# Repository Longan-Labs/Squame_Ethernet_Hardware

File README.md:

Resources of [Squame Ethernet](https://www.longan-labs.cc/catalogsearch/result/?q=squama)

Include:

1. Eagle File
1. Datasheet for W5500

Click on [Longan-Labs.cc](https://www.longan-labs.cc/) to get the product you need.

Contact [support@longan-labs.cc](support@longan-labs.cc) if you need help.

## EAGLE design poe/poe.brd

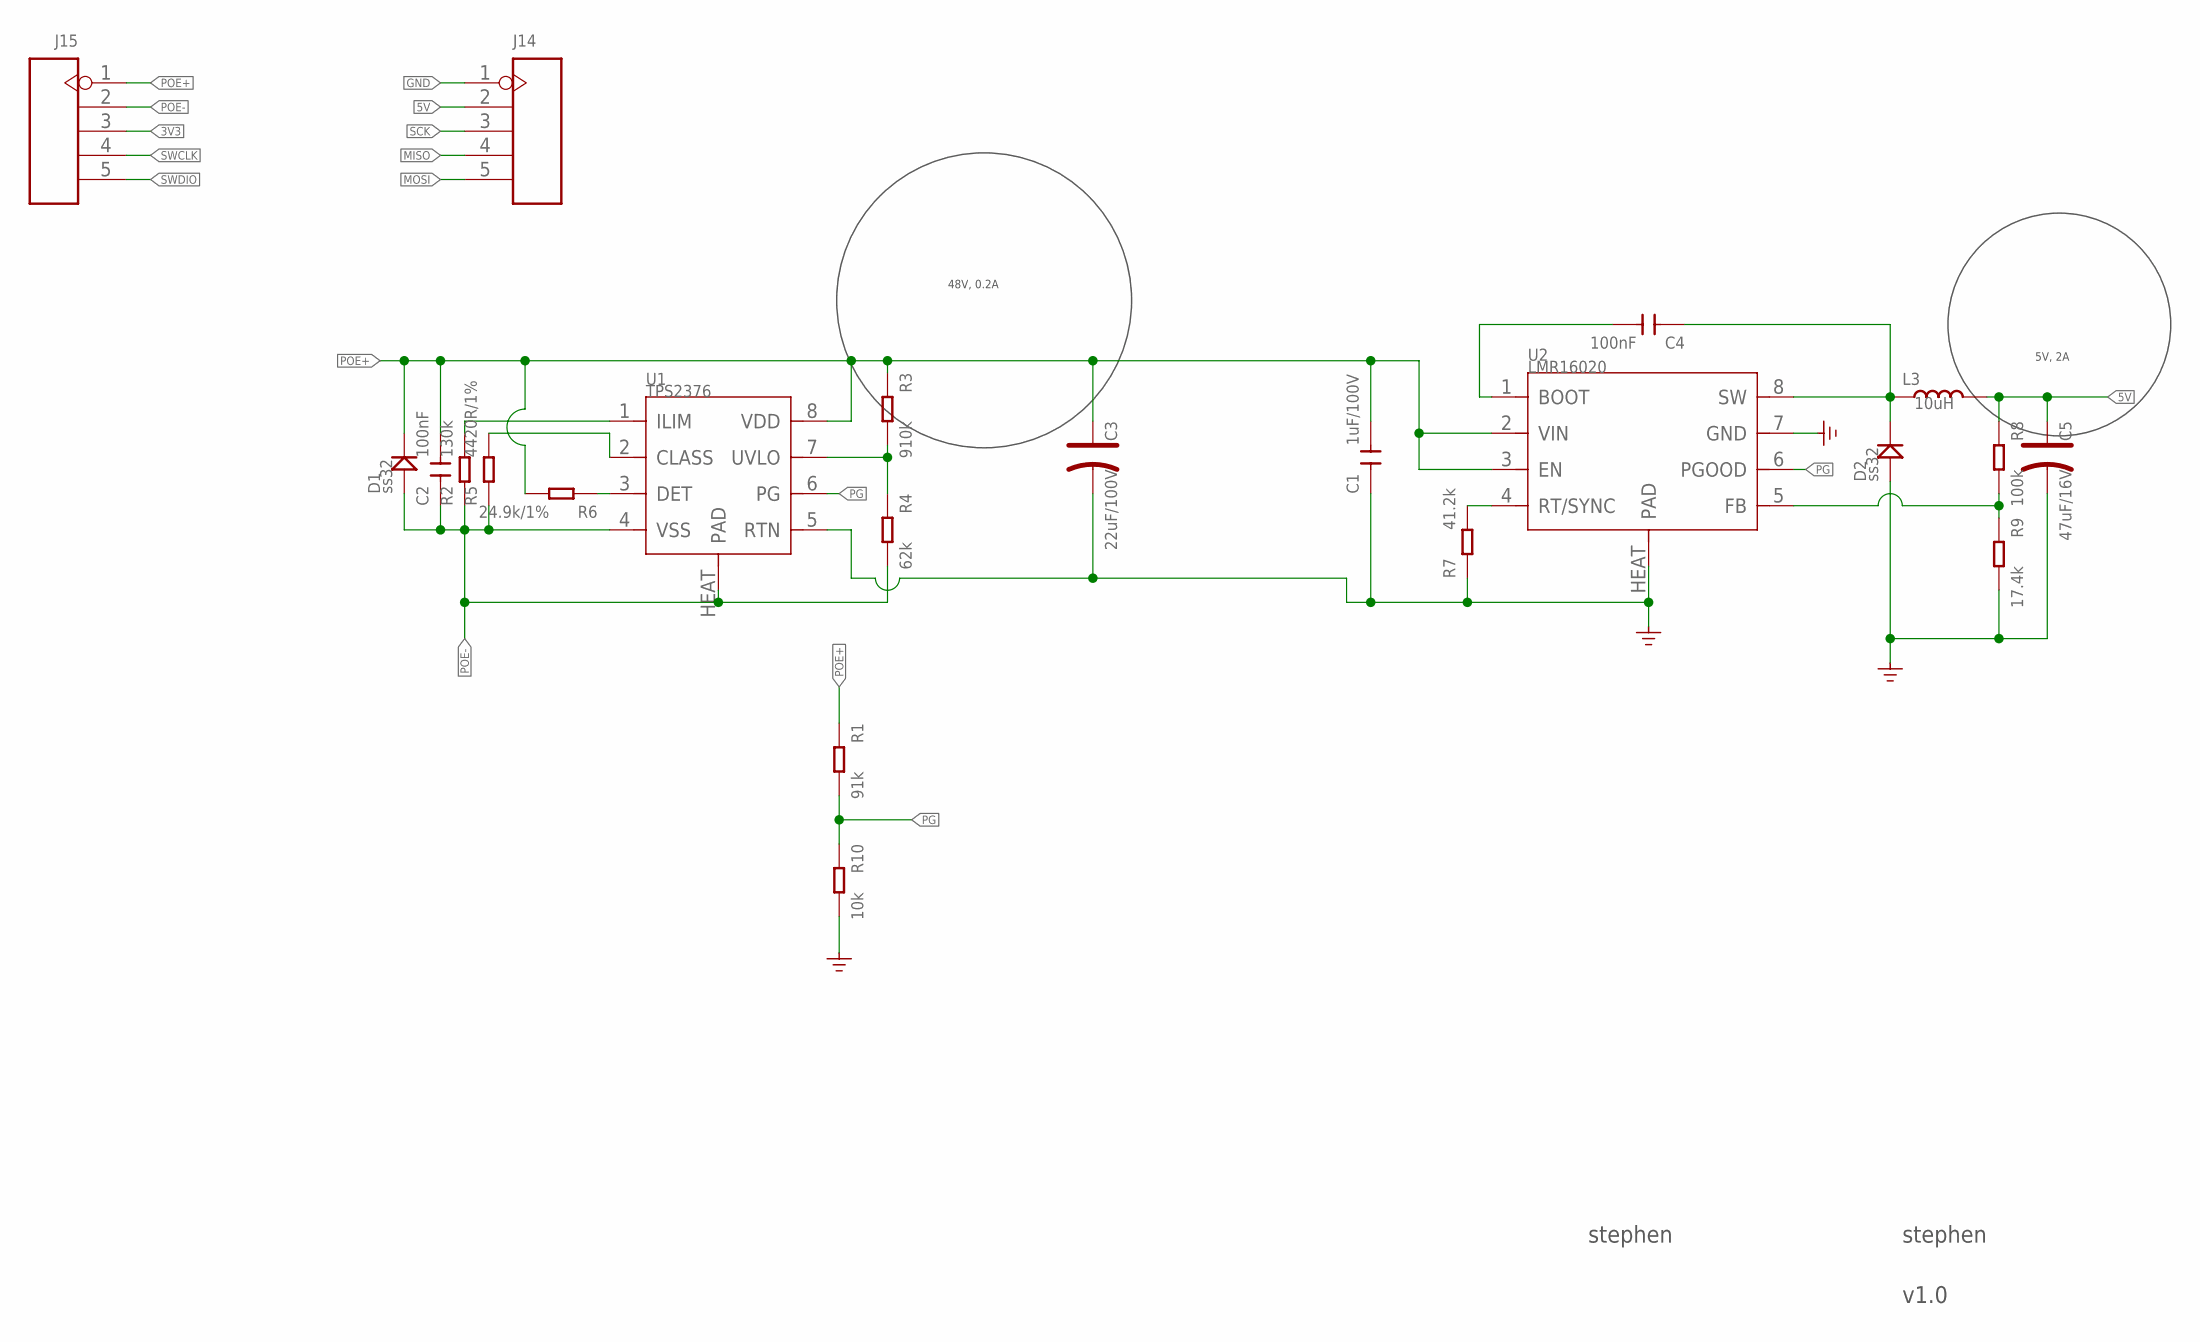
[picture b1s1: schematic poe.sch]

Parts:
C1: 1uF/100V; C0805
C2: 100nF; C0805
C3: 22uF/100V; ELECTRO-SMD-E-7.8MM
C4: 100nF; C0603
C5: 47uF/16V; AVX-B
D1, D2: ss32; DO-214AC
J14, J15: HEADER-5P-2.0; H5-2.0
L3: 10uH; INT2-SMD-6.6X7.1X3MM
R1: 91k; R0603
R2: 130k; R0603
R3: 910k; R0603
R4: 62k; R0603
R5: 4420R/1%; R0603
R6: 24.9k/1%; R0603
R7: 41.2k; R0603
R8: 100k; R0603
R9: 17.4k; R0603
R10: 10k; R0603
U1: TPS2376; SOP8G-1.27-5X3.9MM
U2: LMR16020; SOP8G-1.27-5X3.9MM

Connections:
3V3: J15.3
5V: C5.+, J14.2, L3.2, R8.1
GND: C1.1, C3.-, C5.-, D2.1 (+), J14.1, R7.1, R9.2, R10.2, U1.5 (RTN), U2.7 (GND), U2.HEAT (PAD)
MISO: J14.4
MOSI: J14.5
unnamed: R2.2, U1.1 (ILIM)
unnamed: R5.2, U1.2 (CLASS)
unnamed: R6.1, U1.3 (DET)
unnamed: C4.2, U2.1 (BOOT)
unnamed: R3.2, R4.1, U1.7 (UVLO)
unnamed: R7.2, U2.4 (RT/SYNC)
unnamed: R8.2, R9.1, U2.5 (FB)
unnamed: C4.1, D2.2 (-), L3.1, U2.8 (SW)
PG: R1.2, R10.1, U1.6 (PG), U2.6 (PGOOD)
POE+: C1.2, C2.2, C3.+, D1.2 (-), J15.1, R1.1, R3.1, R6.2, U1.8 (VDD), U2.2 (VIN), U2.3 (EN)
POE-: C2.1, D1.1 (+), J15.2, R2.1, R4.2, R5.1, U1.4 (VSS), U1.HEAT (PAD)
SCK: J14.3
SWCLK: J15.4
SWDIO: J15.5

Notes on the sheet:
stephen
v1.0
48V, 0.2A
5V, 2A

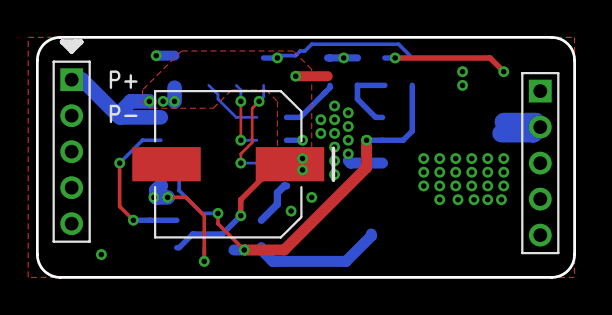
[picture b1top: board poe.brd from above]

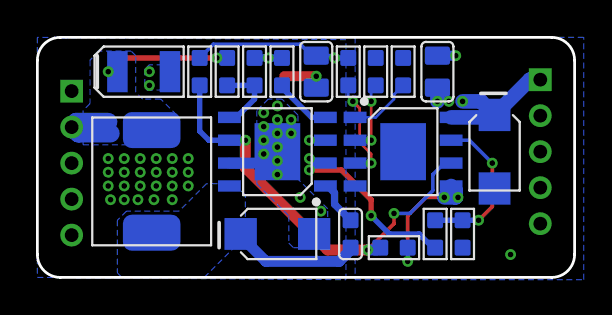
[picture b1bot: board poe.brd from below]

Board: 2 copper layers, 29.8 x 13.3 mm, 22 parts (19 on the bottom side), 13 nets.

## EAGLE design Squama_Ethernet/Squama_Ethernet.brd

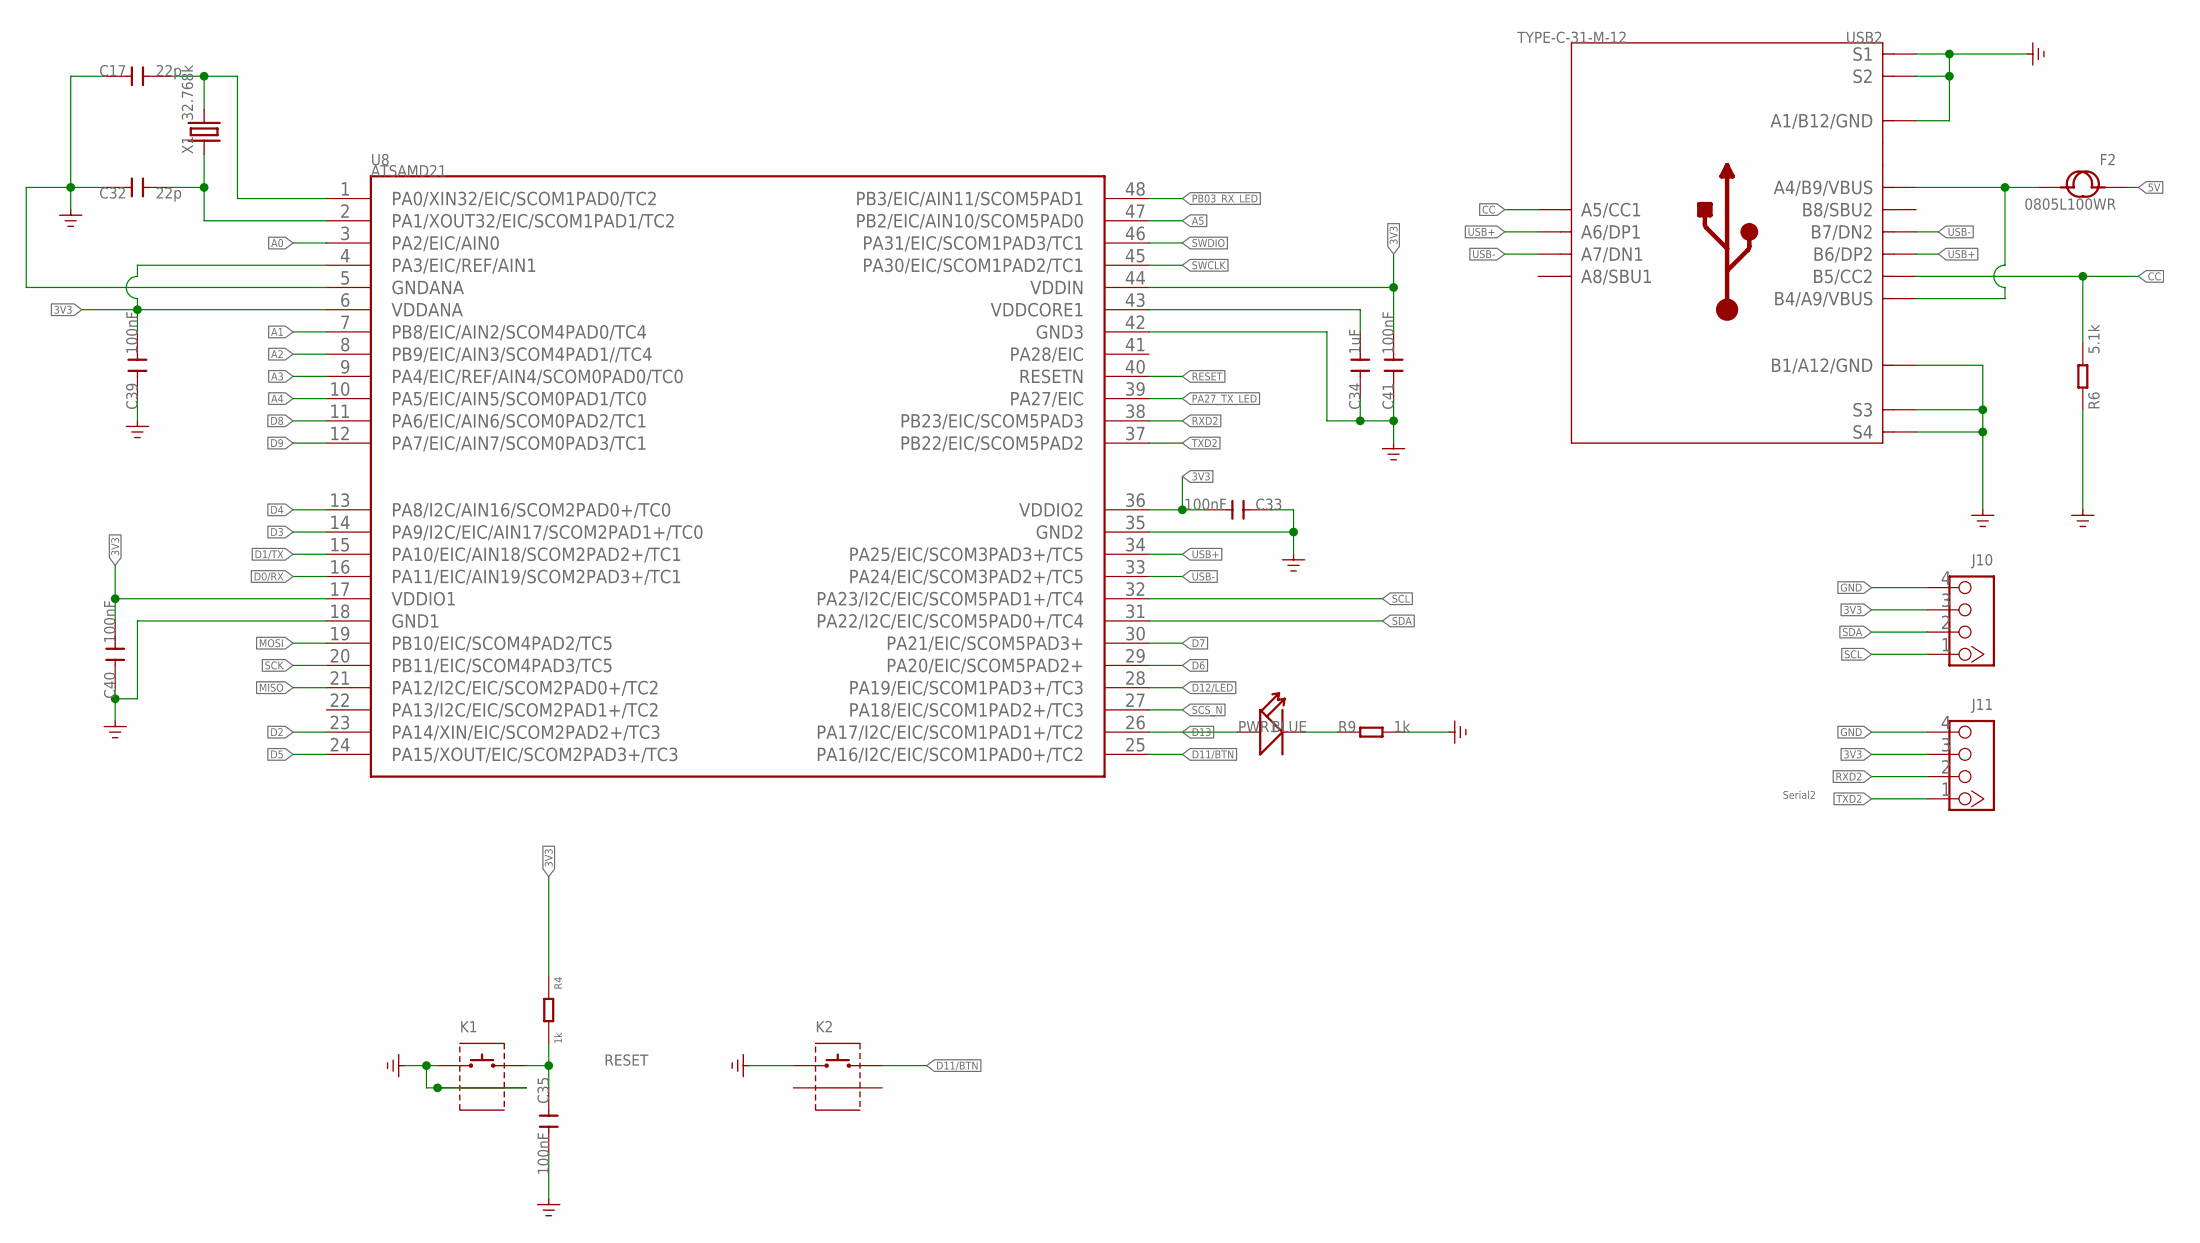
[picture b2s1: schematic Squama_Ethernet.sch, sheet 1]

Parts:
C17, C32: 22p; C0603
C33, C35, C39, C40, C41: 100nF; C0603
C34: 1uF; C0603
F2: 0805L100WR; F0805
J10, J11: 320110033; HW4-2.0
K1, K2: BUTTON-2+2P; SW2+2P-7.7X2.75X3.95MM
PWR1: BLUE; LED-0603
R4, R9: 1k; R0603
R6: 5.1k; R0603
U8: ATSAMD21; TQFP48-0.5-7X7MM
USB2: TYPE-C-31-M-12; USB2.0-TYPE-C
X1: 32.768k; X2-SMD-3.2X1.5X0.55MM

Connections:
3V3: C33.2, C39.2, C40.2, C41.2, J10.3, J11.3, R4.1, U8.4 (PA3/EIC/REF/AIN1), U8.6 (VDDANA), U8.17 (VDDIO1), U8.36 (VDDIO2), U8.44 (VDDIN); also elsewhere on the board
5V: F2.1; also elsewhere on the board
A0: U8.3 (PA2/EIC/AIN0); also elsewhere on the board
A1: U8.7 (PB8/EIC/AIN2/SCOM4PAD0/TC4); also elsewhere on the board
A2: U8.8 (PB9/EIC/AIN3/SCOM4PAD1//TC4)
A3: U8.9 (PA4/EIC/REF/AIN4/SCOM0PAD0/TC0)
A4: U8.10 (PA5/EIC/AIN5/SCOM0PAD1/TC0)
A5: U8.47 (PB2/EIC/AIN10/SCOM5PAD0)
CC: R6.2, USB2.A5 (A5/CC1), USB2.B5 (B5/CC2)
D0/RX: U8.16 (PA11/EIC/AIN19/SCOM2PAD3+/TC1); also elsewhere on the board
D1/TX: U8.15 (PA10/EIC/AIN18/SCOM2PAD2+/TC1); also elsewhere on the board
D2: U8.23 (PA14/XIN/EIC/SCOM2PAD2+/TC3); also elsewhere on the board
D3: U8.14 (PA9/I2C/EIC/AIN17/SCOM2PAD1+/TC0); also elsewhere on the board
D4: U8.13 (PA8/I2C/AIN16/SCOM2PAD0+/TC0); also elsewhere on the board
D5: U8.24 (PA15/XOUT/EIC/SCOM2PAD3+/TC3); also elsewhere on the board
D6: U8.29 (PA20/EIC/SCOM5PAD2+); also elsewhere on the board
D7: U8.30 (PA21/EIC/SCOM5PAD3+); also elsewhere on the board
D8: U8.11 (PA6/EIC/AIN6/SCOM0PAD2/TC1)
D9: U8.12 (PA7/EIC/AIN7/SCOM0PAD3/TC1)
D11/BTN: K2.2, U8.25 (PA16/I2C/EIC/SCOM1PAD0+/TC2)
D12/LED: U8.28 (PA19/EIC/SCOM1PAD3+/TC3); also elsewhere on the board
D13: PWR1.+, U8.26 (PA17/I2C/EIC/SCOM1PAD1+/TC2)
GND: C17.2, C32.2, C33.1, C34.1, C35.2, C39.1, C40.1, C41.1, J10.4, J11.4, K1.1, K1.S1, K1.S2, K2.1, R6.1, R9.2, U8.5 (GNDANA), U8.18 (GND1), U8.35 (GND2), U8.42 (GND3), USB2.A1_B12 (A1/B12/GND), USB2.B1_A12 (B1/A12/GND), USB2.S1, USB2.S2, USB2.S3, USB2.S4, USB2.S5 (S1), USB2.S6 (S2); also elsewhere on the board
MISO: U8.21 (PA12/I2C/EIC/SCOM2PAD0+/TC2); also elsewhere on the board
MOSI: U8.19 (PB10/EIC/SCOM4PAD2/TC5); also elsewhere on the board
unnamed: PWR1.-, R9.1
unnamed: F2.2, USB2.A4_B9 (A4/B9/VBUS), USB2.B4_A9 (B4/A9/VBUS)
unnamed: C17.1, U8.1 (PA0/XIN32/EIC/SCOM1PAD0/TC2), X1.2
unnamed: C32.1, U8.2 (PA1/XOUT32/EIC/SCOM1PAD1/TC2), X1.1
unnamed: C34.2, U8.43 (VDDCORE1)
PA27_TX_LED: U8.39 (PA27/EIC)
PB03_RX_LED: U8.48 (PB3/EIC/AIN11/SCOM5PAD1)
RESET: C35.1, K1.2, R4.2, U8.40 (RESETN)
RXD2: J11.2, U8.38 (PB23/EIC/SCOM5PAD3)
SCK: U8.20 (PB11/EIC/SCOM4PAD3/TC5); also elsewhere on the board
SCL: J10.1, U8.32 (PA23/I2C/EIC/SCOM5PAD1+/TC4)
SCS_N: U8.27 (PA18/EIC/SCOM1PAD2+/TC3); also elsewhere on the board
SDA: J10.2, U8.31 (PA22/I2C/EIC/SCOM5PAD0+/TC4)
SWCLK: U8.45 (PA30/EIC/SCOM1PAD2/TC1); also elsewhere on the board
SWDIO: U8.46 (PA31/EIC/SCOM1PAD3/TC1); also elsewhere on the board
TXD2: J11.1, U8.37 (PB22/EIC/SCOM5PAD2)
USB+: U8.34 (PA25/EIC/SCOM3PAD3+/TC5), USB2.A6 (A6/DP1), USB2.B6 (B6/DP2)
USB-: U8.33 (PA24/EIC/SCOM3PAD2+/TC5), USB2.A7 (A7/DN1), USB2.B7 (B7/DN2)

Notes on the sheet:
Serial2

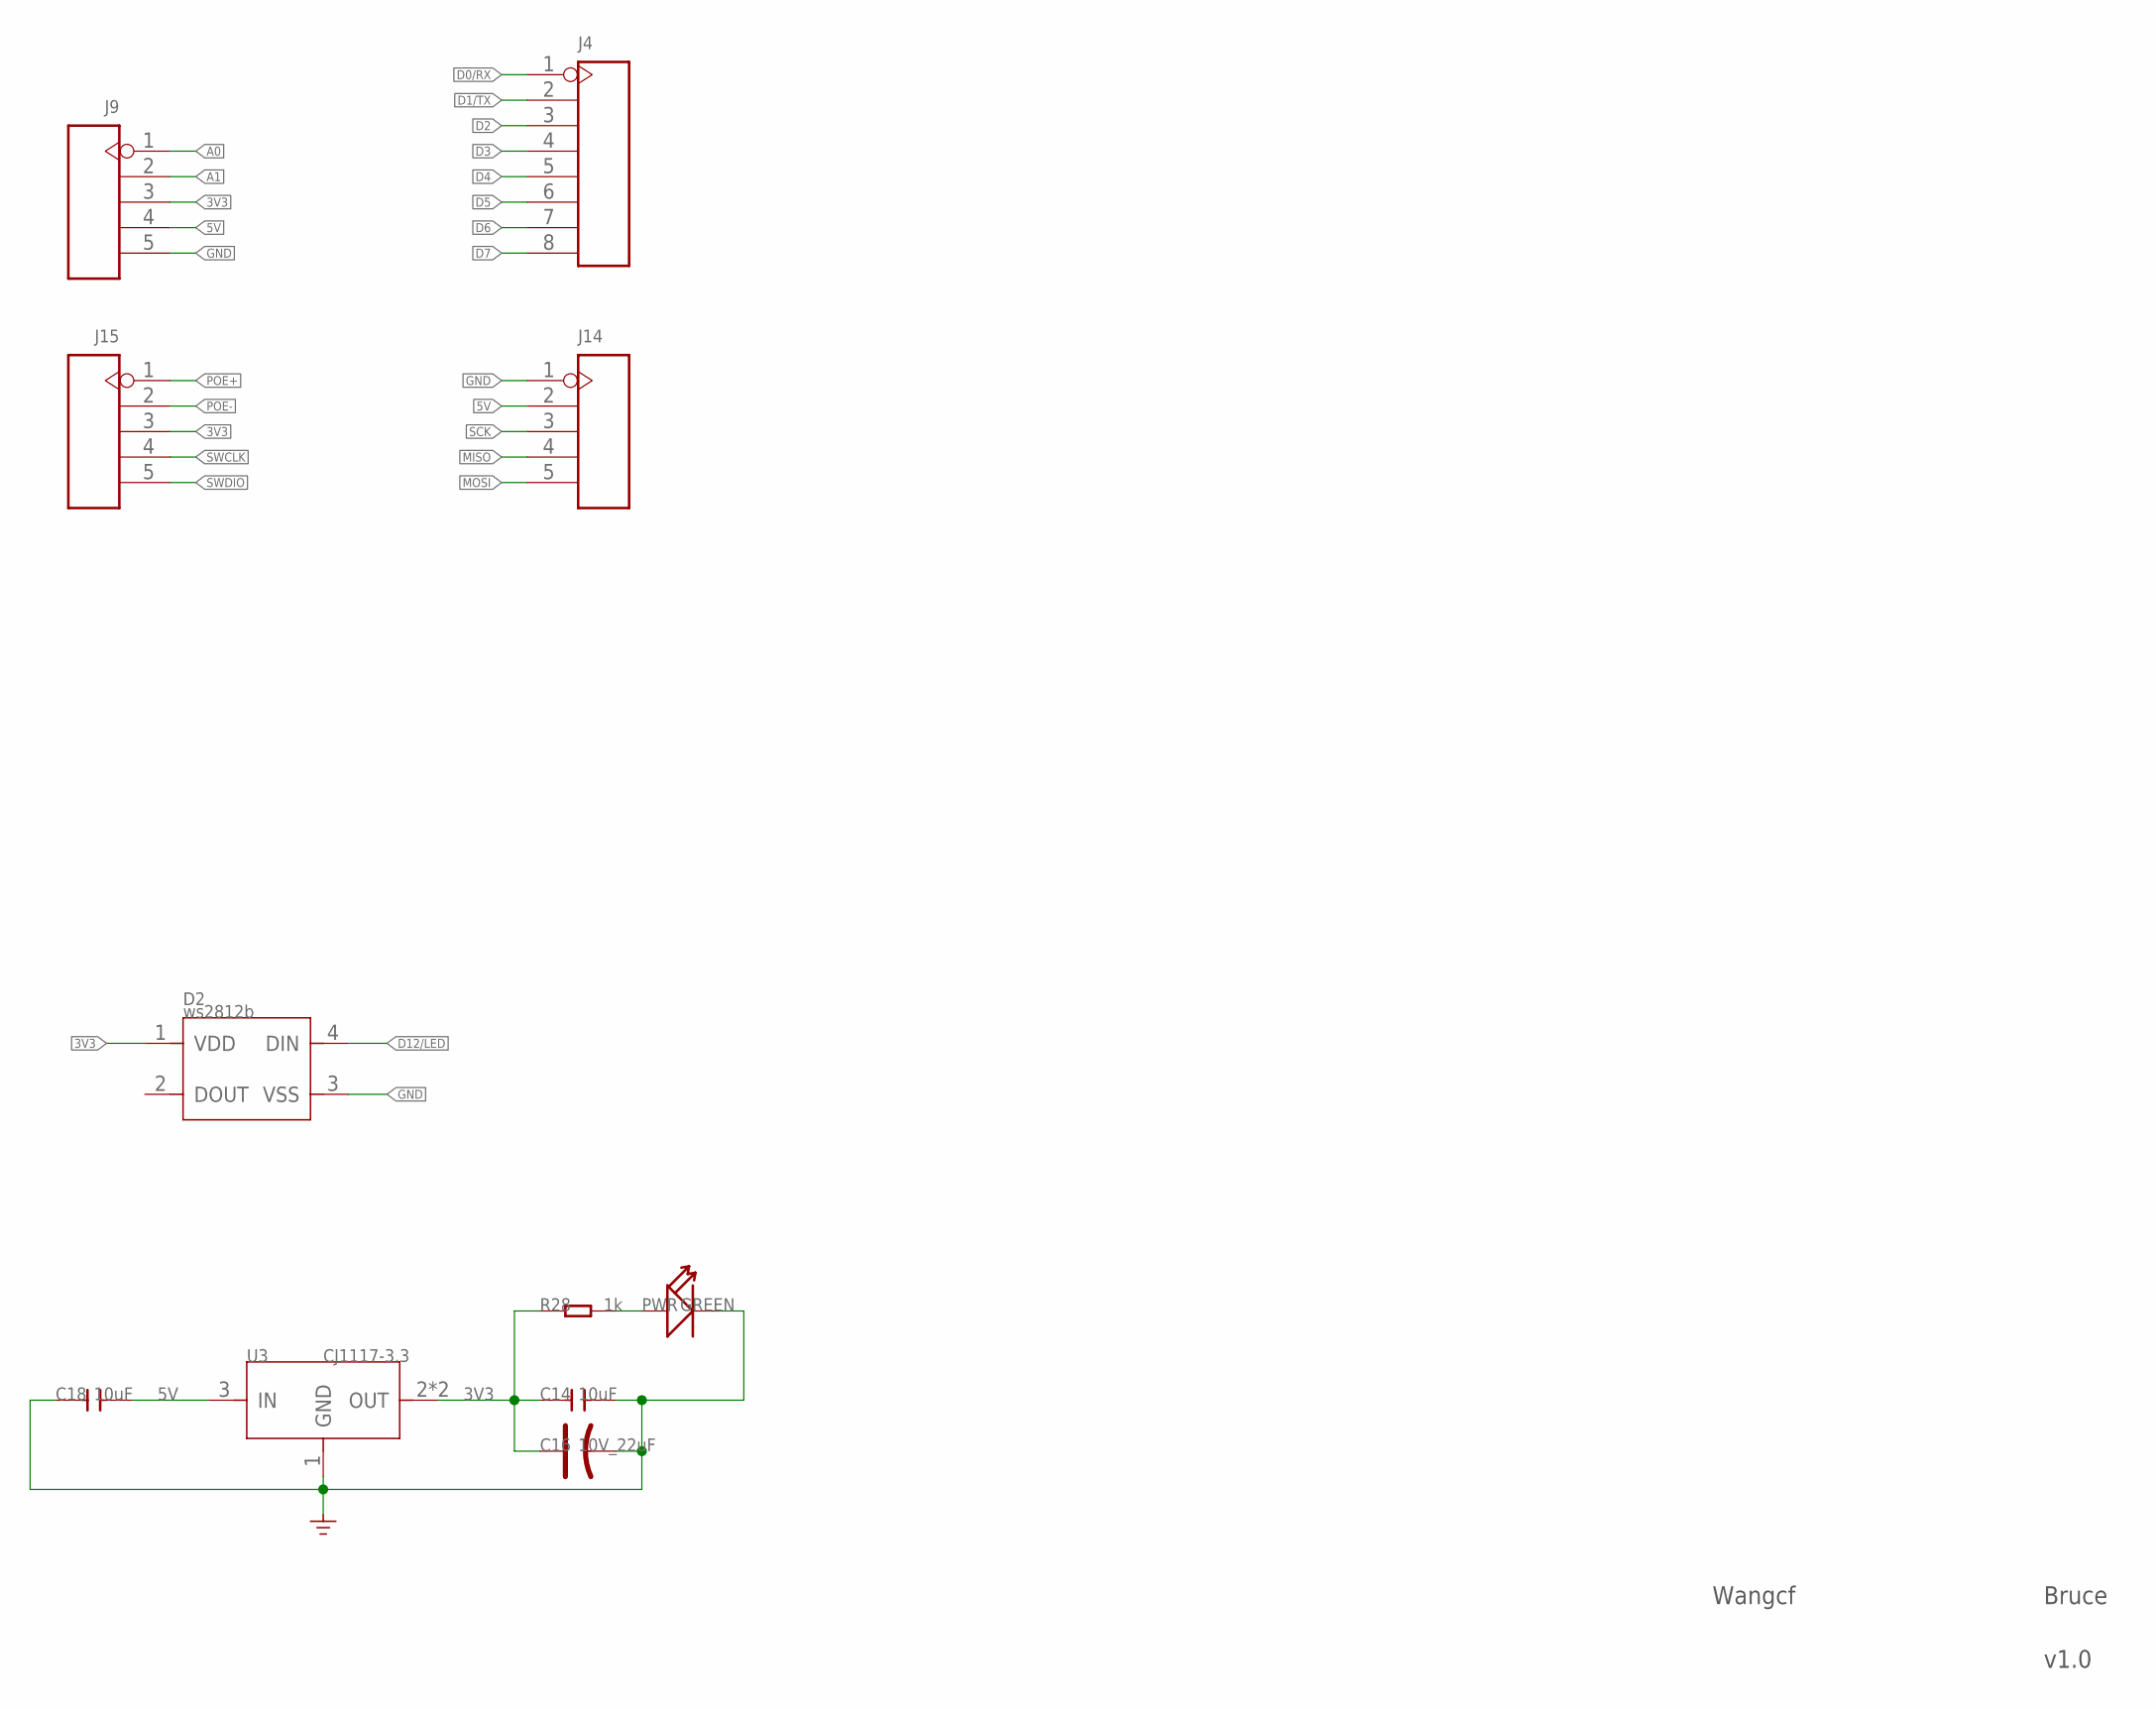
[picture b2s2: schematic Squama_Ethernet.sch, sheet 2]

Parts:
C14, C18: 10uF; C0805
C16: 10V_22uF; AVX-B
D2: ws2812b; LED4-SMD-5050
J4: HEADER-8P-80/40MIL; H8-2.54-C80D40MIL
J9: HEADER-5P-2.54; H5-2.54
J14, J15: HEADER-5P-2.0; H5-2.0
PWR: GREEN; LED-0603
R28: 1k; R0603
U3: CJ1117-3.3; SOT-89

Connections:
3V3: C14.1, C16.+, D2.1 (VDD), J9.3, J15.3, R28.1, U3.2 (OUT), U3.4 (OUT); also elsewhere on the board
5V: C18.2, J9.4, J14.2, U3.3 (IN); also elsewhere on the board
A0: J9.1; also elsewhere on the board
A1: J9.2; also elsewhere on the board
D0/RX: J4.1; also elsewhere on the board
D1/TX: J4.2; also elsewhere on the board
D2: J4.3; also elsewhere on the board
D3: J4.4; also elsewhere on the board
D4: J4.5; also elsewhere on the board
D5: J4.6; also elsewhere on the board
D6: J4.7; also elsewhere on the board
D7: J4.8; also elsewhere on the board
D12/LED: D2.4 (DIN); also elsewhere on the board
GND: C14.2, C16.-, C18.1, D2.3 (VSS), J9.5, J14.1, PWR.-, U3.1 (GND); also elsewhere on the board
MISO: J14.4; also elsewhere on the board
MOSI: J14.5; also elsewhere on the board
unnamed: PWR.+, R28.2
POE+: J15.1; also elsewhere on the board
POE-: J15.2; also elsewhere on the board
SCK: J14.3; also elsewhere on the board
SWCLK: J15.4; also elsewhere on the board
SWDIO: J15.5; also elsewhere on the board

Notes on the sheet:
Wangcf
Bruce
v1.0

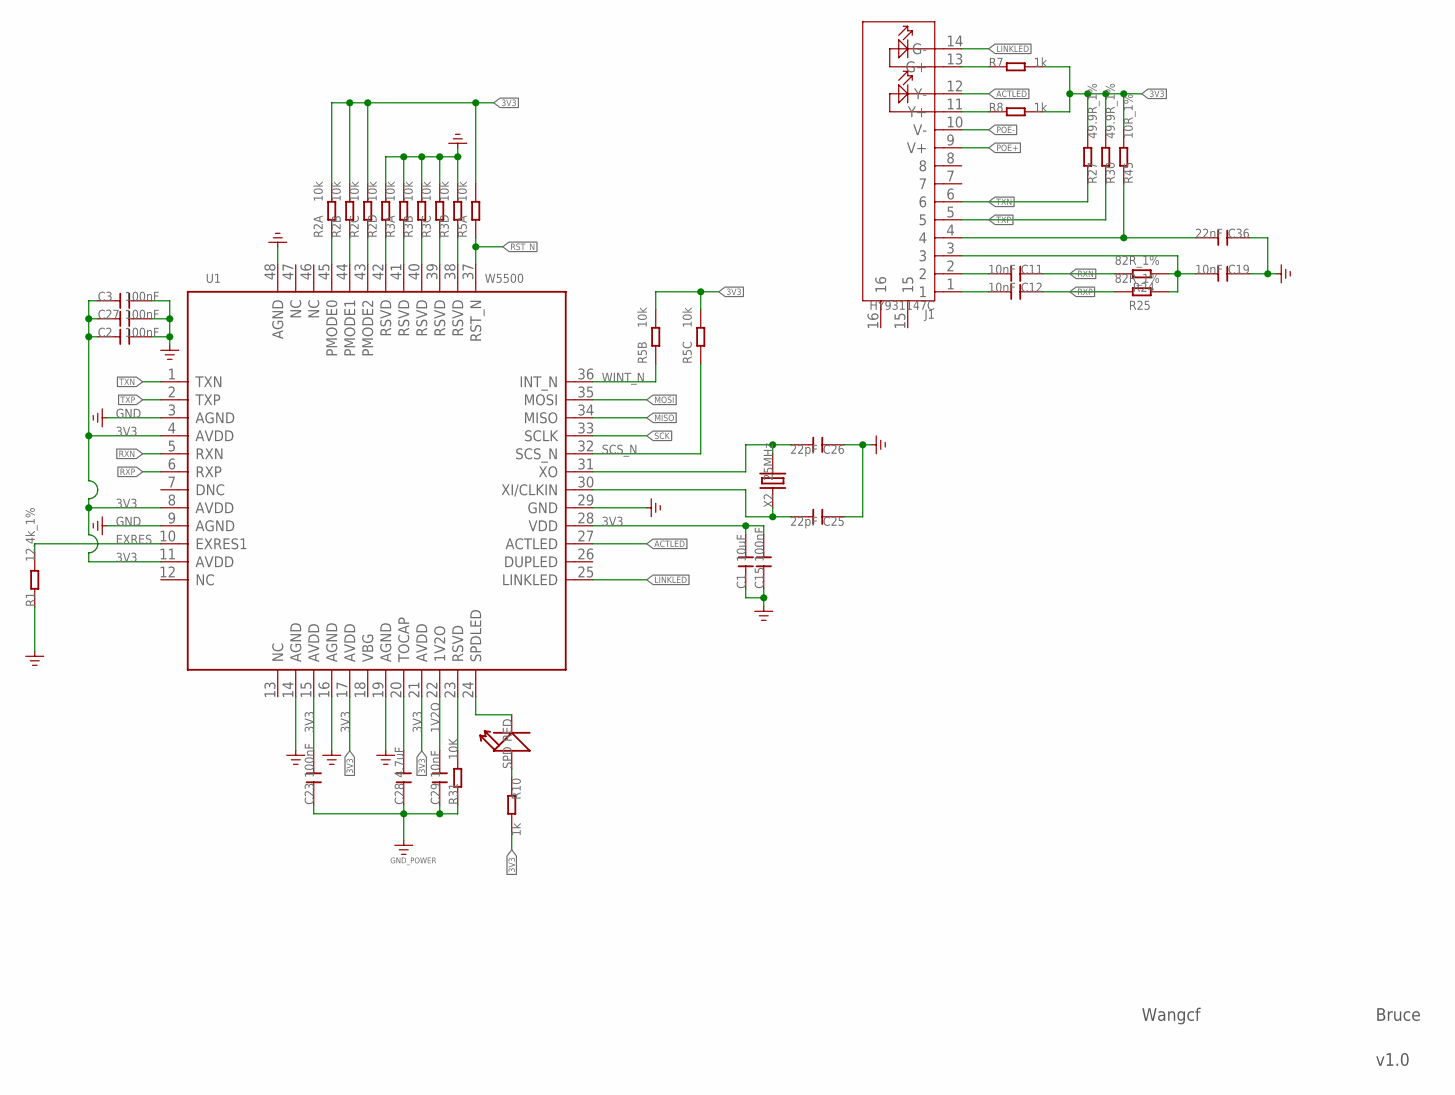
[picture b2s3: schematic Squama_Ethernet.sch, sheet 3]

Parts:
C1: 10uF; C0603
C2, C3, C15, C23, C27: 100nF; C0603
C11, C12, C19, C29: 10nF; C0603
C25, C26: 22pF; C0603
C28: 4.7uF; C0805
C36: 22nF; C0603
J1: HY931147C; RJ45-14+2P-16.1X21.6X13.95MM
R1: 12.4k_1%; R0603
R2, R3, R5: 10k; R0804-8
R7, R8, R10: 1k; R0603
R24, R25: 82R_1%; R0603
R27, R30: 49.9R_1%; R0603
R31: 10K; R0603
R45: 10R_1%; R0603
SPD: RED; LED-0603
U1: W5500; LQFP-48
X2: 25MHz; 2P-SMD-5X3.2

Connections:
1V2O: C29.2, U1.22 (1V2O)
3V3: C1.2, C2.1, C3.1, C15.2, C23.2, C27.1, R2.6 (2), R2.7 (2), R2.8 (2), R5.6 (2), R5.7 (2), R5.8 (2), R7.2, R8.2, R10.2, R27.2, R30.2, R45.2, U1.4 (AVDD), U1.8 (AVDD), U1.11 (AVDD), U1.15 (AVDD), U1.17 (AVDD), U1.21 (AVDD), U1.28 (VDD); also elsewhere on the board
ACTLED: J1.12 (Y-), U1.27 (ACTLED)
EXRES: R1.2, U1.10 (EXRES1)
GND: C1.1, C2.2, C3.2, C15.1, C19.1, C23.1, C25.1, C26.1, C27.2, C28.1, C29.1, C36.1, R1.1, R2.5 (2), R3.5 (2), R3.6 (2), R3.7 (2), R3.8 (2), R31.1, U1.3 (AGND), U1.9 (AGND), U1.14 (AGND), U1.16 (AGND), U1.19 (AGND), U1.29 (GND), U1.48 (AGND); also elsewhere on the board
LINKLED: J1.14 (G-), U1.25 (LINKLED)
MISO: U1.34 (MISO); also elsewhere on the board
MOSI: U1.35 (MOSI); also elsewhere on the board
unnamed: C25.2, U1.30 (XI/CLKIN), X2.1
unnamed: J1.13 (G+), R7.1
unnamed: J1.11 (Y+), R8.1
unnamed: R10.1, SPD.+
unnamed: SPD.-, U1.24 (SPDLED)
unnamed: C36.2, J1.4, R45.1
unnamed: C11.2, J1.2
unnamed: C12.2, J1.1
unnamed: R3.4 (1), U1.38 (RSVD)
unnamed: R3.3 (1), U1.39 (RSVD)
unnamed: R3.2 (1), U1.40 (RSVD)
unnamed: R3.1, U1.41 (RSVD)
unnamed: R2.4 (1), U1.42 (RSVD)
unnamed: C19.2, J1.3, R24.2, R25.1
unnamed: R2.3 (1), U1.43 (PMODE2)
unnamed: R2.2 (1), U1.44 (PMODE1)
unnamed: R2.1, U1.45 (PMODE0)
unnamed: R31.2, U1.23 (RSVD)
POE+: J1.9 (V+); also elsewhere on the board
POE-: J1.10 (V-); also elsewhere on the board
RST_N: R5.1, U1.37 (RST_N)
RXN: C11.1, R24.1, U1.5 (RXN)
RXP: C12.1, R25.2, U1.6 (RXP)
SCK: U1.33 (SCLK); also elsewhere on the board
SCS_N: R5.3 (1), U1.32 (SCS_N); also elsewhere on the board
TOCAP: C28.2, U1.20 (TOCAP)
TXN: J1.6, R27.1, U1.1 (TXN)
TXP: J1.5, R30.1, U1.2 (TXP)
WINT_N: R5.2 (1), U1.36 (INT_N)
XO: C26.2, U1.31 (XO), X2.2

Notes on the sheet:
Wangcf
Bruce
v1.0

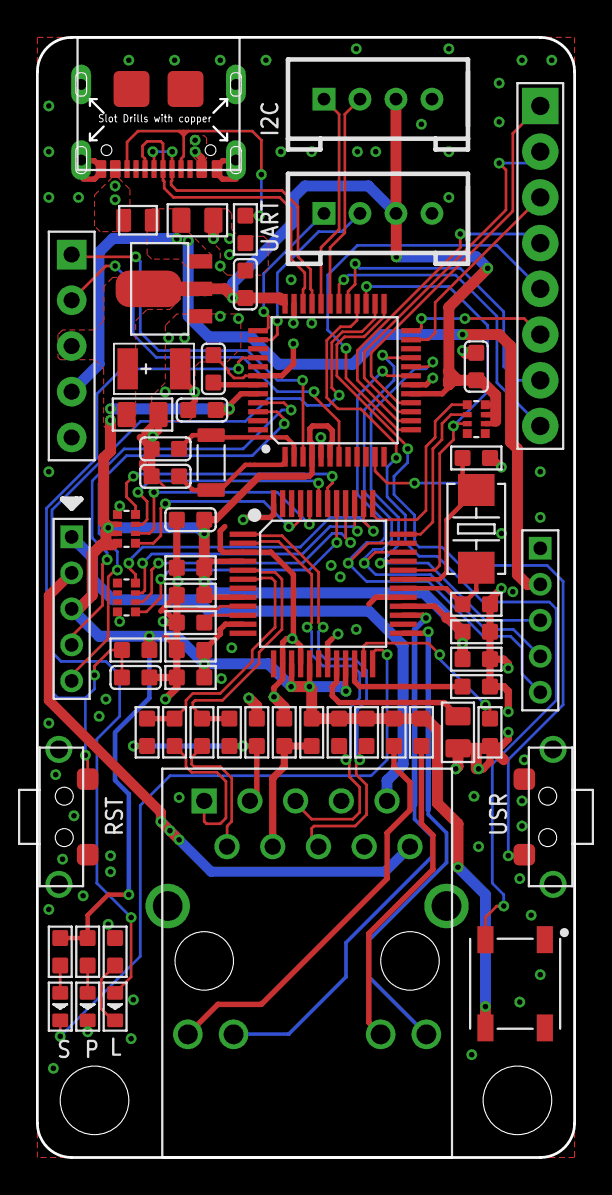
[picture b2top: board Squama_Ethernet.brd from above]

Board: 2 copper layers, 29.8 x 62.2 mm, 63 parts (1 on the bottom side), 68 nets.

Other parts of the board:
U$7: LONGAN-SILK-SMALLER

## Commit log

2021-01-04 add datasheet
